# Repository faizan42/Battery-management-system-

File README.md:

# Battery-management-system-
Battery management system which improve charging time. Using this circuit we can charge the coin-cell or lipo battery 60% fast then normal charging.Here i have used SMD component only for make in small size. This PCB is double sided.And also attached the BOM and presentation in latex.

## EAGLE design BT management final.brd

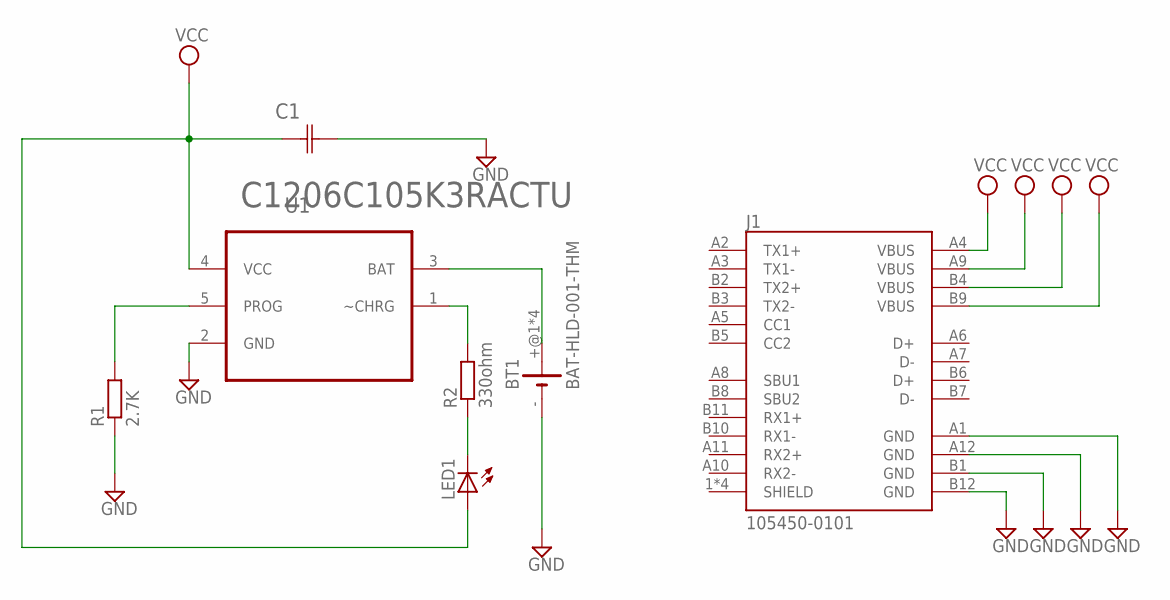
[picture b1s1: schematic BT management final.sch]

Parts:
BT1: BAT-HLD-001-THM; LINX_BAT-HLD-001-THM
C1: C1206C105K3RACTU; CAPC3216X175N
J1: 105450-0101; MOLEX_105450-0101
LED1: LED_ESML0603; LED_SML0603
R1: 2.7K; R0603
R2: 330ohm; R0603
U1: LTC4054LES5-4.2TRPBF; SOT95P280X100-5N

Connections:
GND: BT1.-, C1.2 (C2), J1.A1 (GND), J1.A12 (GND), J1.B1 (GND), J1.B12 (GND), R1.1, U1.2 (GND)
unnamed: R1.2, U1.5 (PROG)
unnamed: R2.2, U1.1 (~CHRG)
unnamed: LED1.C, R2.1
unnamed: BT1.+@1 (+), BT1.+@2 (+), BT1.+@3 (+), BT1.+@4 (+), U1.3 (BAT)
SHIELD: J1.1 (SHIELD), J1.2 (SHIELD), J1.3 (SHIELD), J1.4 (SHIELD)
VCC: C1.1 (C1), J1.A4 (VBUS), J1.A9 (VBUS), J1.B4 (VBUS), J1.B9 (VBUS), LED1.A, U1.4 (VCC)

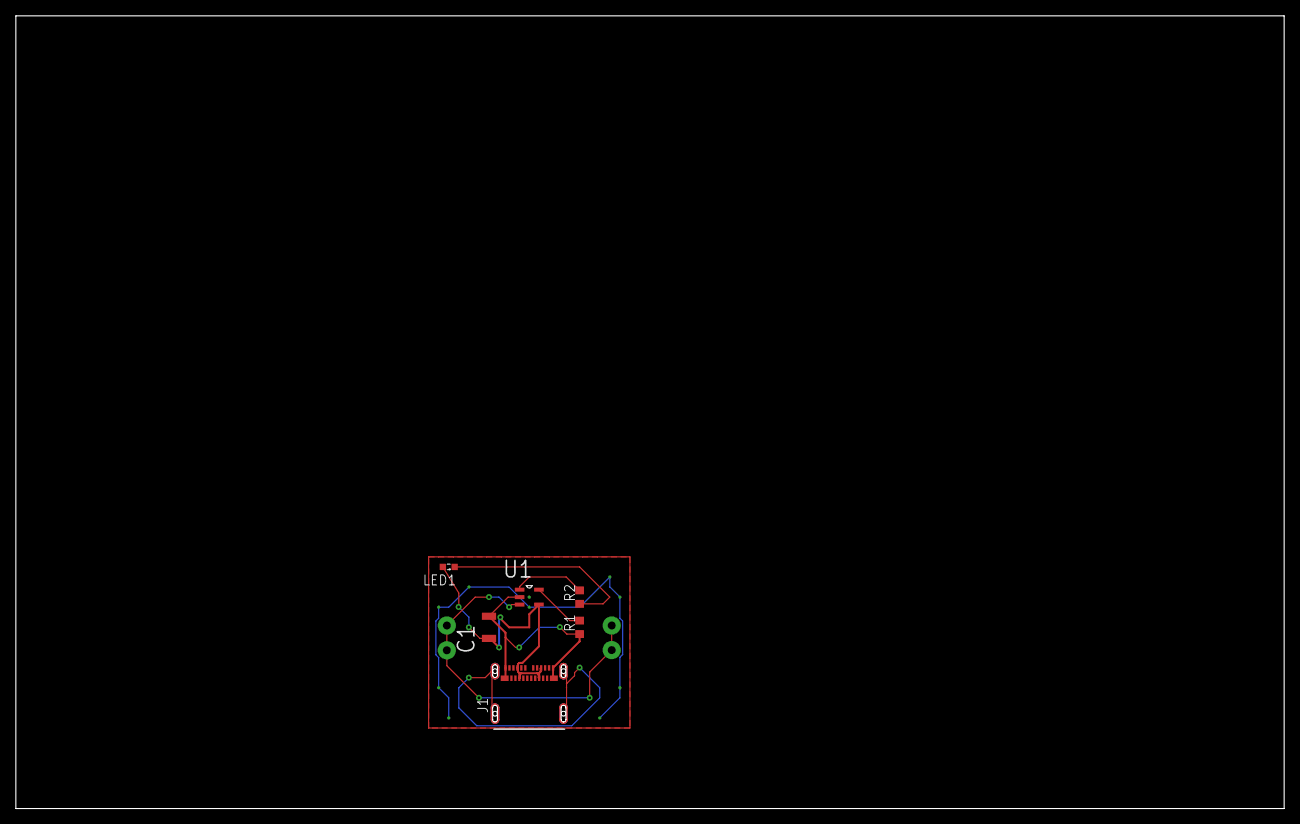
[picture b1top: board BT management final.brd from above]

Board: 2 copper layers, 160.0 x 100.0 mm, 7 parts (1 on the bottom side), 7 nets.
